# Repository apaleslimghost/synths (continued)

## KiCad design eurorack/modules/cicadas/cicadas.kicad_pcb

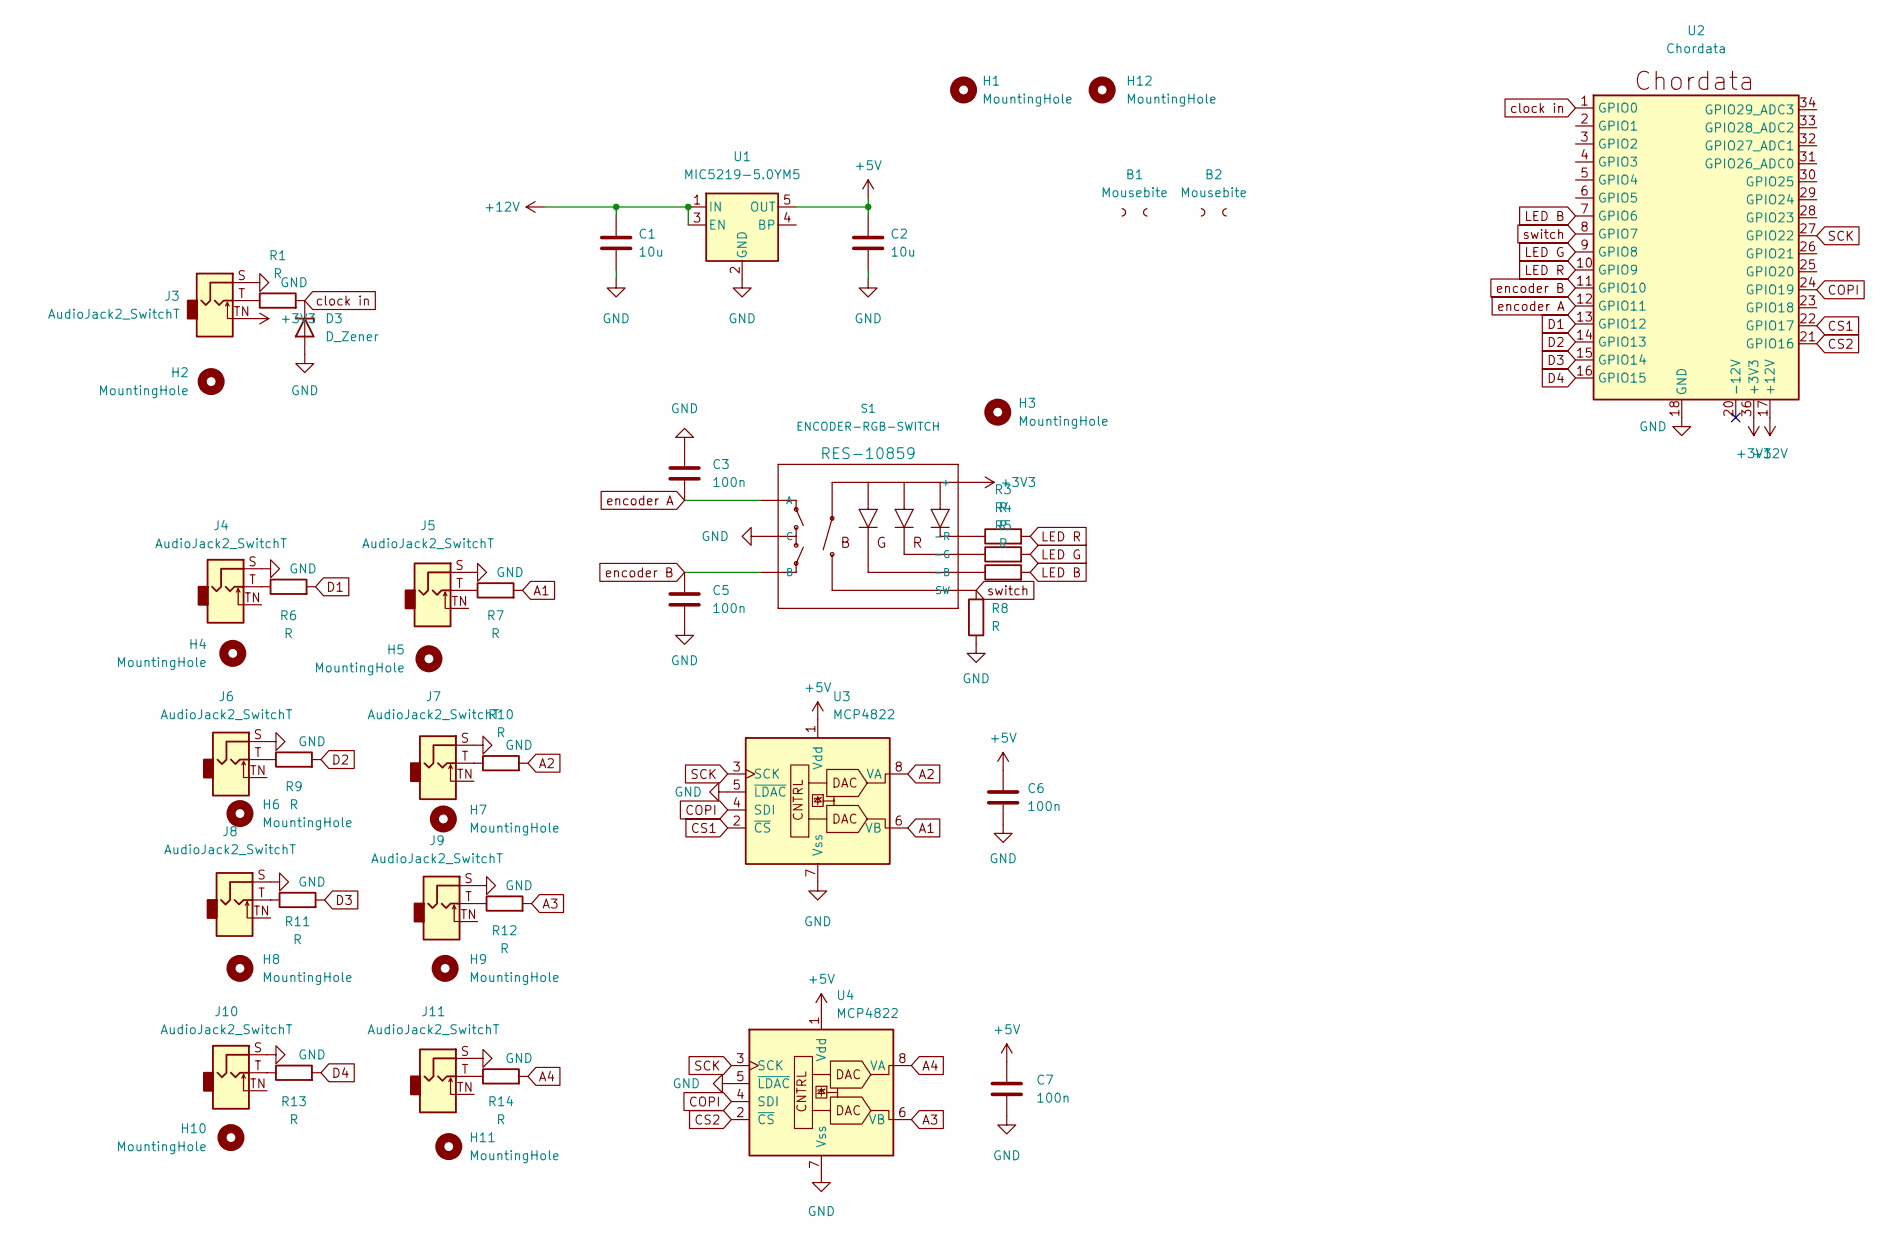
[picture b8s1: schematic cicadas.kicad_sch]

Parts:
B1, B2: Mousebite; mousebite-2.54x5.08mm
C1, C2: 10u; C_0805_2012Metric_Pad1.18x1.45mm_HandSolder
C3, C5, C6, C7: 100n; C_0805_2012Metric_Pad1.18x1.45mm_HandSolder
D3: D_Zener; D_0805_2012Metric_Pad1.15x1.40mm_HandSolder
H1, H12: MountingHole; eurorack panel mounting slot
H2, H4, H5, H6, H7, H8, H9, H10, H11: MountingHole; hole 6mm (jack panel)
H3: MountingHole; hole 9mm (encoder panel)
J3, J4, J5, J6, J7, J8, J9, J10, J11: AudioJack2_SwitchT; Jack_3.5mm_QingPu_WQP-PJ398SM_Vertical
R1, R3, R4, R5, R6, R7, R8, R9, R10, R11, R12, R13, R14: R; R_0805_2012Metric_Pad1.20x1.40mm_HandSolder
S1: ENCODER-RGB-SWITCH; ENCODER_LED_3
U1: MIC5219-5.0YM5; SOT-23-5
U2: Chordata
U3, U4: MCP4822; SOIC-8_3.9x4.9mm_P1.27mm

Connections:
+3V3: J3.TN, S1.5 (+), U2.36 (+3V3)
+5V: C2.1, C6.1, C7.1, U1.5 (OUT), U3.1 (Vdd), U4.1 (Vdd)
+12V: C1.1, U1.1 (IN), U1.3 (EN), U2.17 (+12V)
A1: R7.2, U3.6 (VB)
A2: R10.2, U3.8 (VA)
A3: R12.2, U4.6 (VB)
A4: R14.2, U4.8 (VA)
COPI: U2.24 (GPIO19), U3.4 (SDI), U4.4 (SDI)
CS1: U2.22 (GPIO17), U3.2 (~CS)
CS2: U2.21 (GPIO16), U4.2 (~CS)
D1: R6.2, U2.13 (GPIO12)
D2: R9.2, U2.14 (GPIO13)
D3: R11.2, U2.15 (GPIO14)
D4: R13.2, U2.16 (GPIO15)
GND: C1.2, C2.2, C3.1, C5.2, C6.2, C7.2, D3.2 (A), J3.S, J4.S, J5.S, J6.S, J7.S, J8.S, J9.S, J10.S, J11.S, R8.1, S1.C, U1.2 (GND), U2.18 (GND), U2.19 (GND), U2.35 (GND), U3.5 (~LDAC), U3.7 (Vss), U4.5 (~LDAC), U4.7 (Vss)
LED B: R5.2, U2.7 (GPIO6)
LED G: R4.2, U2.9 (GPIO8)
LED R: R3.2, U2.10 (GPIO9)
unnamed: J3.T, R1.1
unnamed: J4.T, R6.1
unnamed: J5.T, R7.1
unnamed: J6.T, R9.1
unnamed: J7.T, R10.1
unnamed: J8.T, R11.1
unnamed: J9.T, R12.1
unnamed: J10.T, R13.1
unnamed: J11.T, R14.1
unnamed: R3.1, S1.1 (-R)
unnamed: R4.1, S1.2 (-G)
unnamed: R5.1, S1.4 (-B)
SCK: U2.27 (GPIO22), U3.3 (SCK), U4.3 (SCK)
clock in: D3.1 (K), R1.2, U2.1 (GPIO0)
encoder A: C3.2, S1.A, U2.12 (GPIO11)
encoder B: C5.1, S1.B, U2.11 (GPIO10)
switch: R8.2, S1.3 (SW), U2.8 (GPIO7)

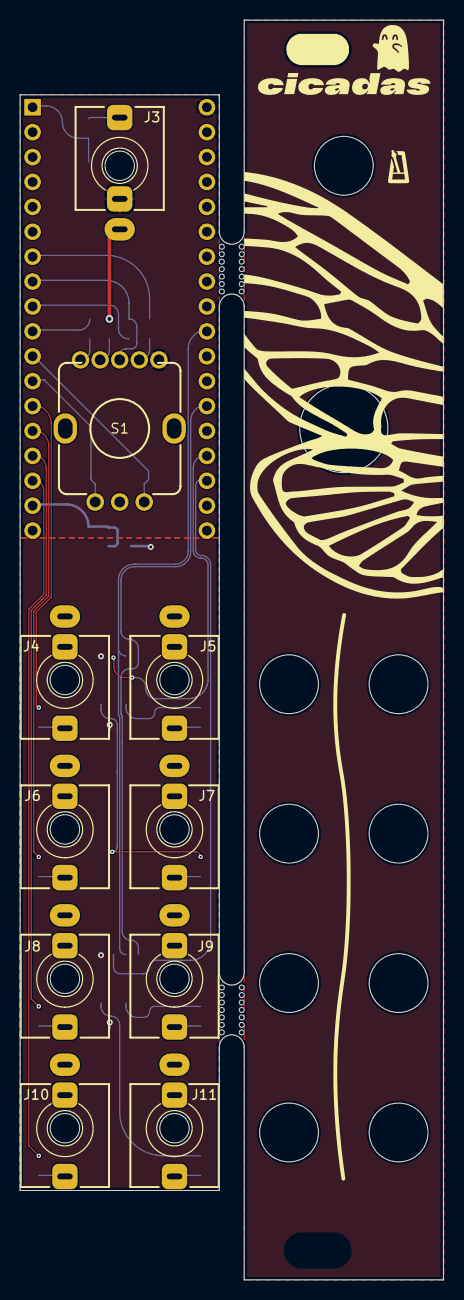
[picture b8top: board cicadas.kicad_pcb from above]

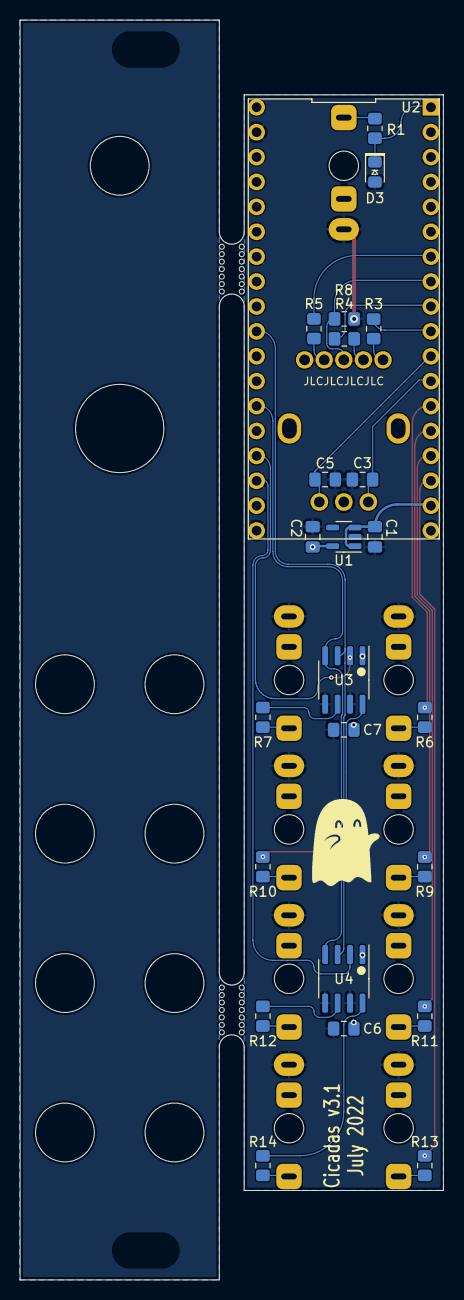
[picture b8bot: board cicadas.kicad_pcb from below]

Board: 2 copper layers, 43.2 x 128.5 mm, 50 parts (25 on the bottom side), 35 nets.

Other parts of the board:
G1: Artwork; LOGO
G2: LOGO

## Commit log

2022-04-10 everything lol
2022-04-10 add readmes and licences
2022-04-10 make logo smaller
2022-04-10 and a bit bigger again
2022-04-11 add github cover image
2022-04-30 initial work on cicadas v3
2022-05-26 add new art to cicadas board
2022-05-31 cicadas footprint associations
2022-05-31 initial work on fireflies
2022-05-31 fireflies schematic stuff
2022-06-02 cicadas: normal clock input to 3v3 and fix missing ground connections
2022-07-15 add chordata
2022-07-22 update gitignore
2022-07-22 final chord organ design
2022-07-22 final chordata v1 layout
2022-07-22 logo stuff
2022-07-22 fix dolphins transistor labels
2022-07-22 no idea
2022-07-22 start rethinking fireflies around chordata
2022-07-22 play with idea of mini-owls
2022-10-26 Backlink to CADLAB.io has been added.
2022-10-26 wip fireflies redesign
2022-10-26 some controller experiments
2022-10-26 i guess i opened hummingbirds in kicad 6
2022-10-26 wip cicadas redesign
2022-10-26 bunch of prototypes
2022-10-26 chordata v2 final layout
2022-11-21 better logo for silkscreen
2022-11-21 bats v2
2022-11-21 final mules v1 design
2022-12-05 ignore autosave files
2022-12-05 what even was that
2022-12-07 i honestly have no idea
2022-12-07 dunno
2022-12-07 chordata plots
2022-12-07 why would you put it at the top of the readme
2022-12-07 hopefully the last spurious file to delete
2022-12-07 add osprey schematic
2022-12-07 more
2022-12-07 add test github pages stuff
2022-12-07 needs to be called docs
2022-12-07 Create CNAME
2022-12-08 move some files around
2022-12-08 test chordata build page
2022-12-08 how do yaml
2022-12-09 local jekyll setup
2022-12-09 basic layout, fonts and styles
2022-12-09 design for markdown files
2022-12-09 formatting
2022-12-09 images always need auto height
2022-12-09 clear image correctly (just needs floats and margins)
2022-12-09 do hyphens to it
2022-12-09 more accurate widths and better spacing
2022-12-09 round images with shadows
2022-12-09 a photo (not a very helpful one tbh)
2022-12-10 favicon
2022-12-10 header
2022-12-10 page titles, tweak spacing
2022-12-10 pages list index
2022-12-10 chordata flashing instructions
2022-12-19 tweak spacing
2023-01-10 add spiders
2023-01-10 svg/png logo exports
2023-01-10 updated favicon
2023-01-11 chordata build guide
2023-01-11 breathing room at the bottom of pages
2023-01-11 only make videos snug with h3s
2023-01-11 link logo to root
2023-01-12 link to flux datasheet
2023-01-12 use flexa mono for code
2023-01-12 uf2 bug was fixed in 13.1
2023-01-12 pinout explanation
2023-01-12 add pinout
2023-01-12 spacing tweaks
2023-01-12 add picture of it plugged in for flashing
2023-01-19 add meta viewport
2023-02-11 spiders panel tweaks
2023-02-11 update cover image
2023-02-11 cicadas panel with new branding
2023-04-15 ants v2 final design
2023-04-15 bus v2
2023-04-15 spiders tweaks
2023-04-15 ants v2 entry boards
2023-04-24 fix chordata pinout diagram :((((
2023-04-28 update chordata bootsel instructions
2023-05-31 add zebras
2023-06-09 initial zebras test firmware including led touch slider implementation
2023-06-09 logo animation
2023-07-23 try debugging zebras firmware
2023-11-10 business card
2023-11-10 final design files for ants ecosystem
2023-11-10 spiders v1 files
2023-11-10 sometimes we call folders gerbers ig
2023-11-10 ravens files
2023-11-10 assorted changes ig from opening things in kicad 7
2023-11-10 oled files
2023-11-10 pigeons
2023-11-10 elephants
2023-11-10 arthropoda
2023-11-10 oops, those are the chordata docs
2023-11-10 cuckoos
2023-11-10 remove panels
2023-11-10 utterly cursed jekyll stuff for a better grouped index page
2024-01-26 add ocelots
2024-01-26 jan 24
2024-05-30 add rudimentary ravens bom
2024-05-30 add front matter to ravens bom
2024-05-30 support full width pages
2024-05-30 actually make fullwidth pages full width
2024-05-30 update ravens bom title and make full width
2024-05-30 fix bom frontmatter yaml
2024-05-31 rudimentary table styling
2024-05-31 section display on page
2024-05-31 remove redundant ravens pRefix
2024-05-31 add ravens index
2025-10-13 elephants manual, just add pictures
2025-10-28 fix liquid syntax in section index
